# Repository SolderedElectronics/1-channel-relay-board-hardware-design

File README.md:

# 1-channel relay board Hardware Design

## About the Product

|  |
| :----------------------------------------------------------: |
| [Buy 1-channel relay board](https://www.solde.red/333024) |

Did you ever want to turn on and off a device that needs large current or voltage? Whether operating on DC or AC, a relay is what you need. A relay is an electronic switch that is activated by a signal we send from a Dasduino or Arduino. This module further simplifies the whole process, because it contains everything you need for the relay to work, and you just have to connect it to the microcontroller and power supply. You don’t even have to think about voltages and currents, insulation between high and low voltage or grounding, everything is already taken care of on the board.

---

## Repository Contents

This repository contains all design files for 1-channel relay board, organized as follows:

- **`CAD` folder**: Contains KiCAD design files, including:
  - Schematics
  - PCB layout
  - Panel PCB layout
  - Source 3D files in Fusion360, if any
  - All files are sorted by version with a detailed change log.
- **`OUTPUTS` folder**: Includes all production-ready files, such as:
  - Bill of Materials (BOM) and interactive BOM (iBOM)
  - PDF versions of schematics
  - 3D `.step` file of the board
  - 3D-printable models
  - Gerber files for PCB manufacturing
  - Image of the pinout of the board
  - Product image
  - Compliance, legal and generic sales documents

Refer to the `Change Log` in the CAD folder for details about updates between versions.

---

## Learn More About the Product

Beyond the repository, explore the following resources:

### Soldered Verify

The **Soldered Verify** system ensures every board you purchase from Soldered is fully functional. It also provides access to exclusive test data for your product. To get started, find the unique Soldered Verify ID on your product's packaging and enter the ID on the [Soldered Verify page](https://soldered.com/verify/) to access test results and additional product details.

### Soldered Community

Soldered Community is your go-to place for technical support. Our engineers track and answer all questions posted there, and it’s a great space for the maker community. Get answers to your questions and solutions for your challenges at [Soldered Community](https://soldered.com/community).

### solde.red

solde.red is an ultimate URL shortener and information hub. Access it by typing solde.red/ followed by your product SKU, e.g., [solde.red/333000](https://solde.red/333000), to find getting-started guides, datasheets, open-source hardware and software files, certifications, images, pinouts, and more. Read more about the shortener [here](https://solde.red/info/).

---

## Contributing

Contributions are welcome! Here’s how you can get involved:

- Submit pull requests to enhance the design or fix issues.
- Report bugs or problems by opening an issue.

We encourage community collaboration to make this product even better.

---

## About Soldered

[Soldered for Makers](https://soldered.com) specializes in designing and manufacturing electronic products tailored for enthusiasts, ranging from hobbyists to professionals. Our portfolio includes electronic boards, sensors, and actuators that are widely utilized in fields such as microelectronics, mechatronics, robotics, programming, and IoT. Every product we offer is designed in-house and built upon open-source hardware and software platforms. Proudly certified and manufactured within the European Union, our catalog likely includes the product you need for your project.

We complement these products with comprehensive tutorials and manuals, product descriptions, schematics, programming codes, and project examples. Our round-the-clock [customer and technical support](https://soldered.com/community) is available for all our products, irrespective of the sales channel. Soldered’s success and services reflect our maker community’s unwavering [trust](https://www.trustpilot.com/review/soldered.com), for which we are deeply grateful. Join our community and create using Soldered products.

---

## License

All Soldered open-source hardware (OSH) is under The TAPR Open Hardware License. Read more in the LICENSE file located in this repository.

**Disclaimer:**

No warranty - all designs in this repository are distributed in the hope that they will be useful, but without any warranty. They are provided "AS IS", therefore without warranty of any kind, either expressed or implied. The entire quality and performance of what you do with the contents of this repository are your responsibility. In no event Soldered Electronics will be liable for your damages, or losses, including any general, special, incidental, or consequential damage arising out of the use or inability to use the contents of this repository. 

---

## Have fun!

Thank you for your support from your fellow makers at Soldered Electronics.

Happy Making!

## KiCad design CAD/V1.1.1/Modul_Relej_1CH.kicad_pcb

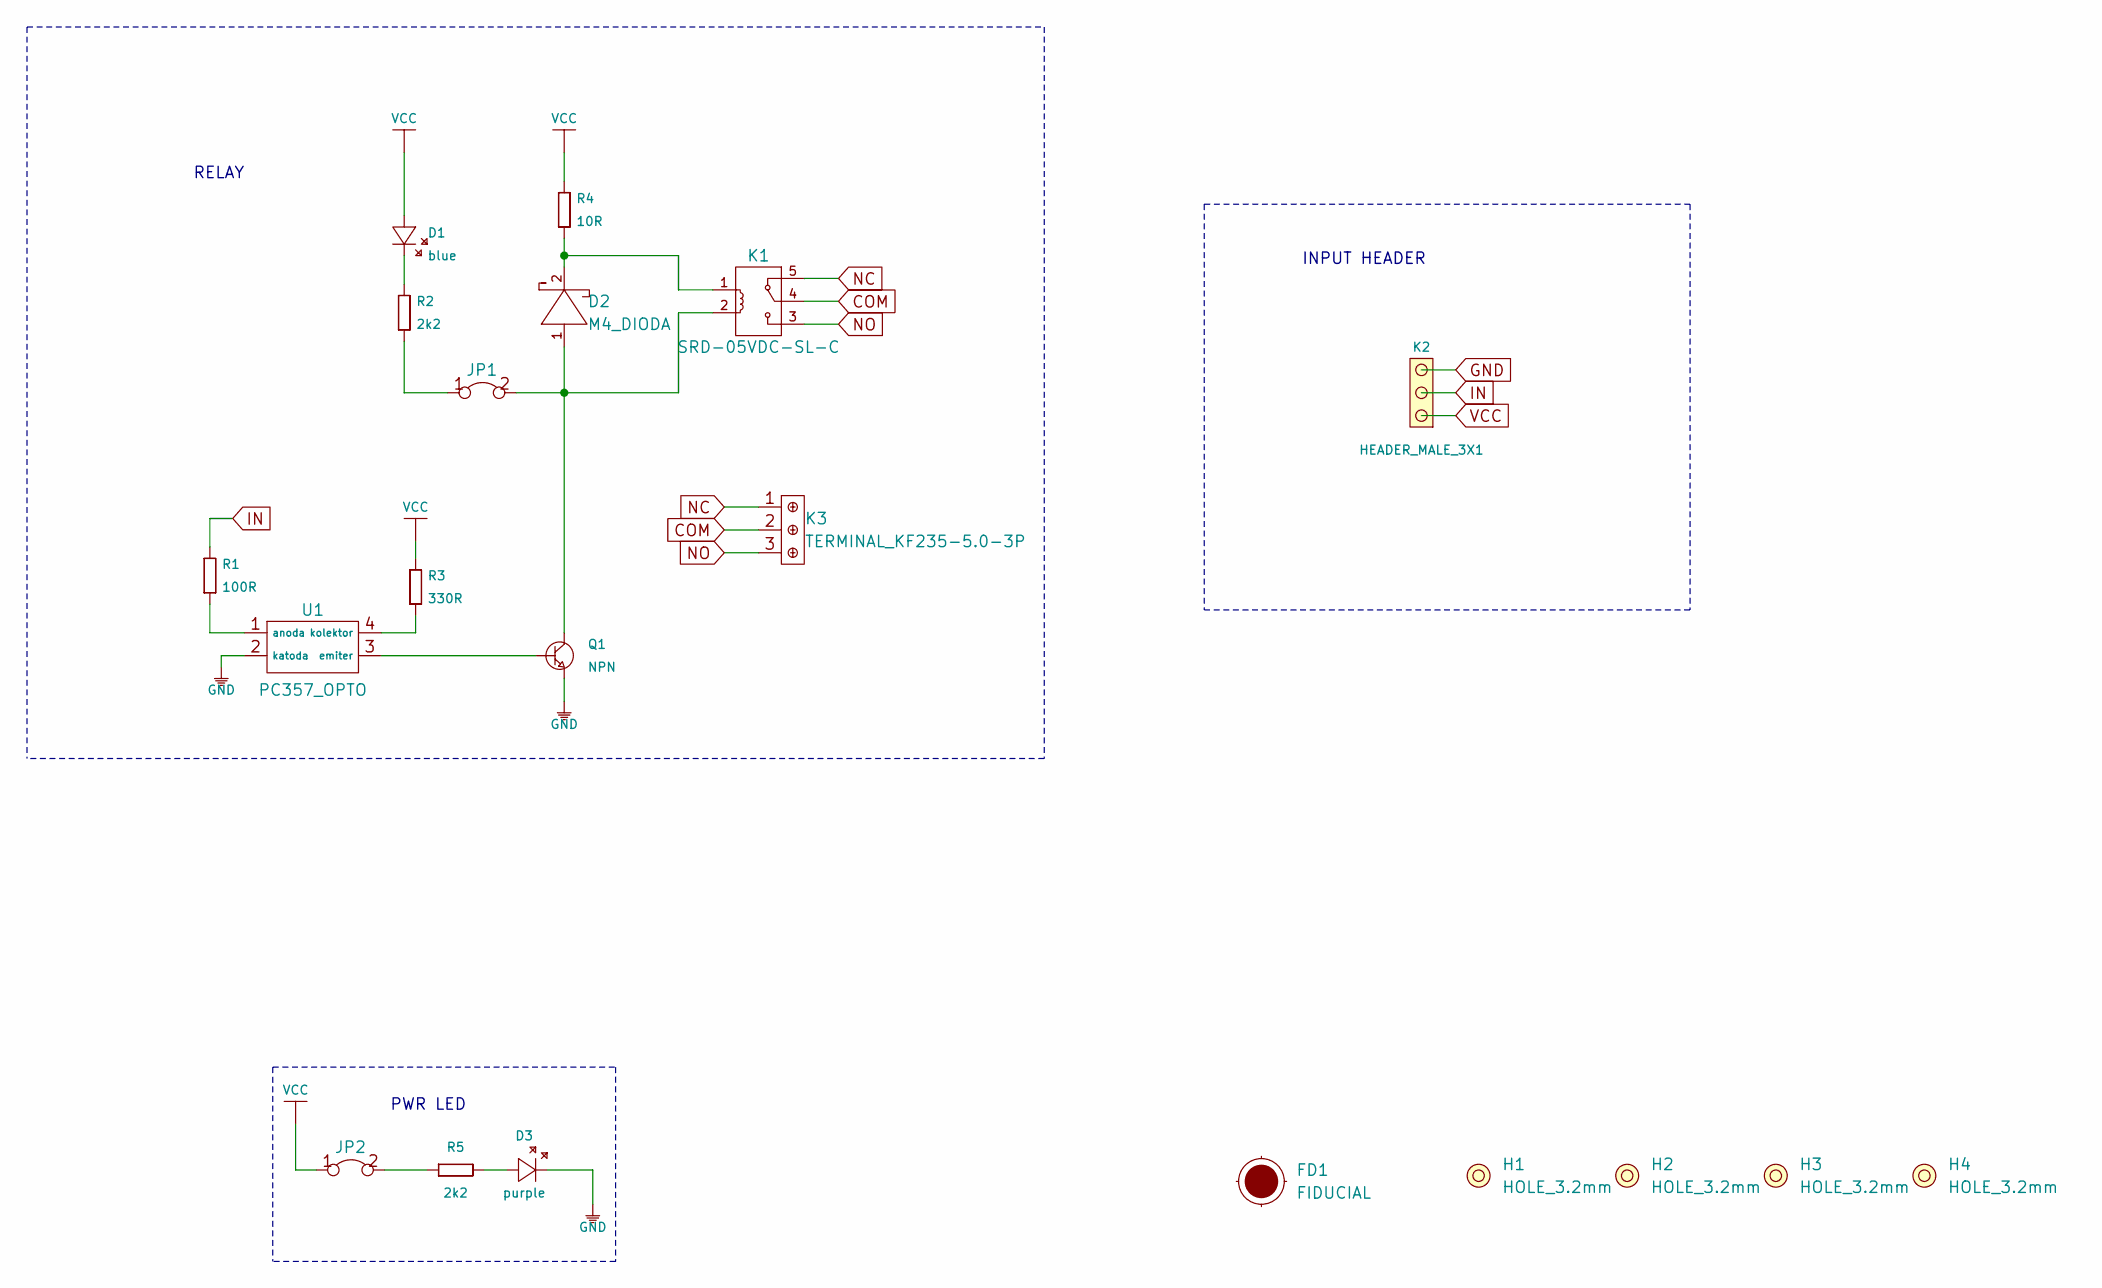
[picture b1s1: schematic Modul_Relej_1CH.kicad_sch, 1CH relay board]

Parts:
D1: blue; 0402LED
D2: M4_DIODA
D3: purple; 0402LED
FD1: FIDUCIAL; FIDUCIAL_23
H1, H2, H3, H4: HOLE_3.2mm
JP1, JP2: SMD-JUMPER-CONNECTED_TRACE_SLODERMASK
K1: SRD-05VDC-SL-C; SRD_RELAY_5V
K2: HEADER_MALE_3X1
K3: TERMINAL_KF235-5.0-3P
Q1: NPN; SOT-23-3
R1: 100R; 0603R
R2, R5: 2k2; 0402R
R3: 330R; 0603R
R4: 10R; 0603R
U1: PC357_OPTO

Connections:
COM: K1.4, K3.2
GND: D3.2 (K), K2.3, Q1.2 (E), U1.2 (katoda)
IN: K2.2, R1.2
NC: K1.5, K3.1
NO: K1.3, K3.3
unnamed: D1.2 (K), R2.2
unnamed: D2.1 (A), JP1.2, K1.2, Q1.3 (C)
unnamed: D2.2 (K), K1.1, R4.1
unnamed: D3.1 (A), R5.2
unnamed: JP1.1, R2.1
unnamed: JP2.2, R5.1
unnamed: Q1.1 (B), U1.3 (emiter)
unnamed: R1.1, U1.1 (anoda)
unnamed: R3.1, U1.4 (kolektor)
VCC: D1.1 (A), JP2.1, K2.1, R3.2, R4.2

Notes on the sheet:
PWR LED
INPUT HEADER
RELAY

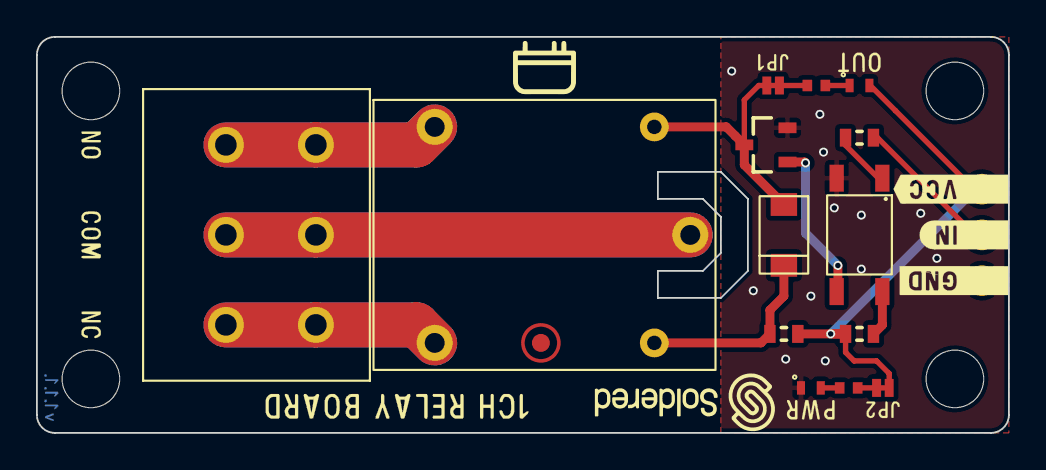
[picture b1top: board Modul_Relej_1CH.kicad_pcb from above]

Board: 2 copper layers, 54.0 x 22.0 mm, 20 parts (1 on the bottom side), 15 nets.

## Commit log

2022-08-06 Updating open source files.
